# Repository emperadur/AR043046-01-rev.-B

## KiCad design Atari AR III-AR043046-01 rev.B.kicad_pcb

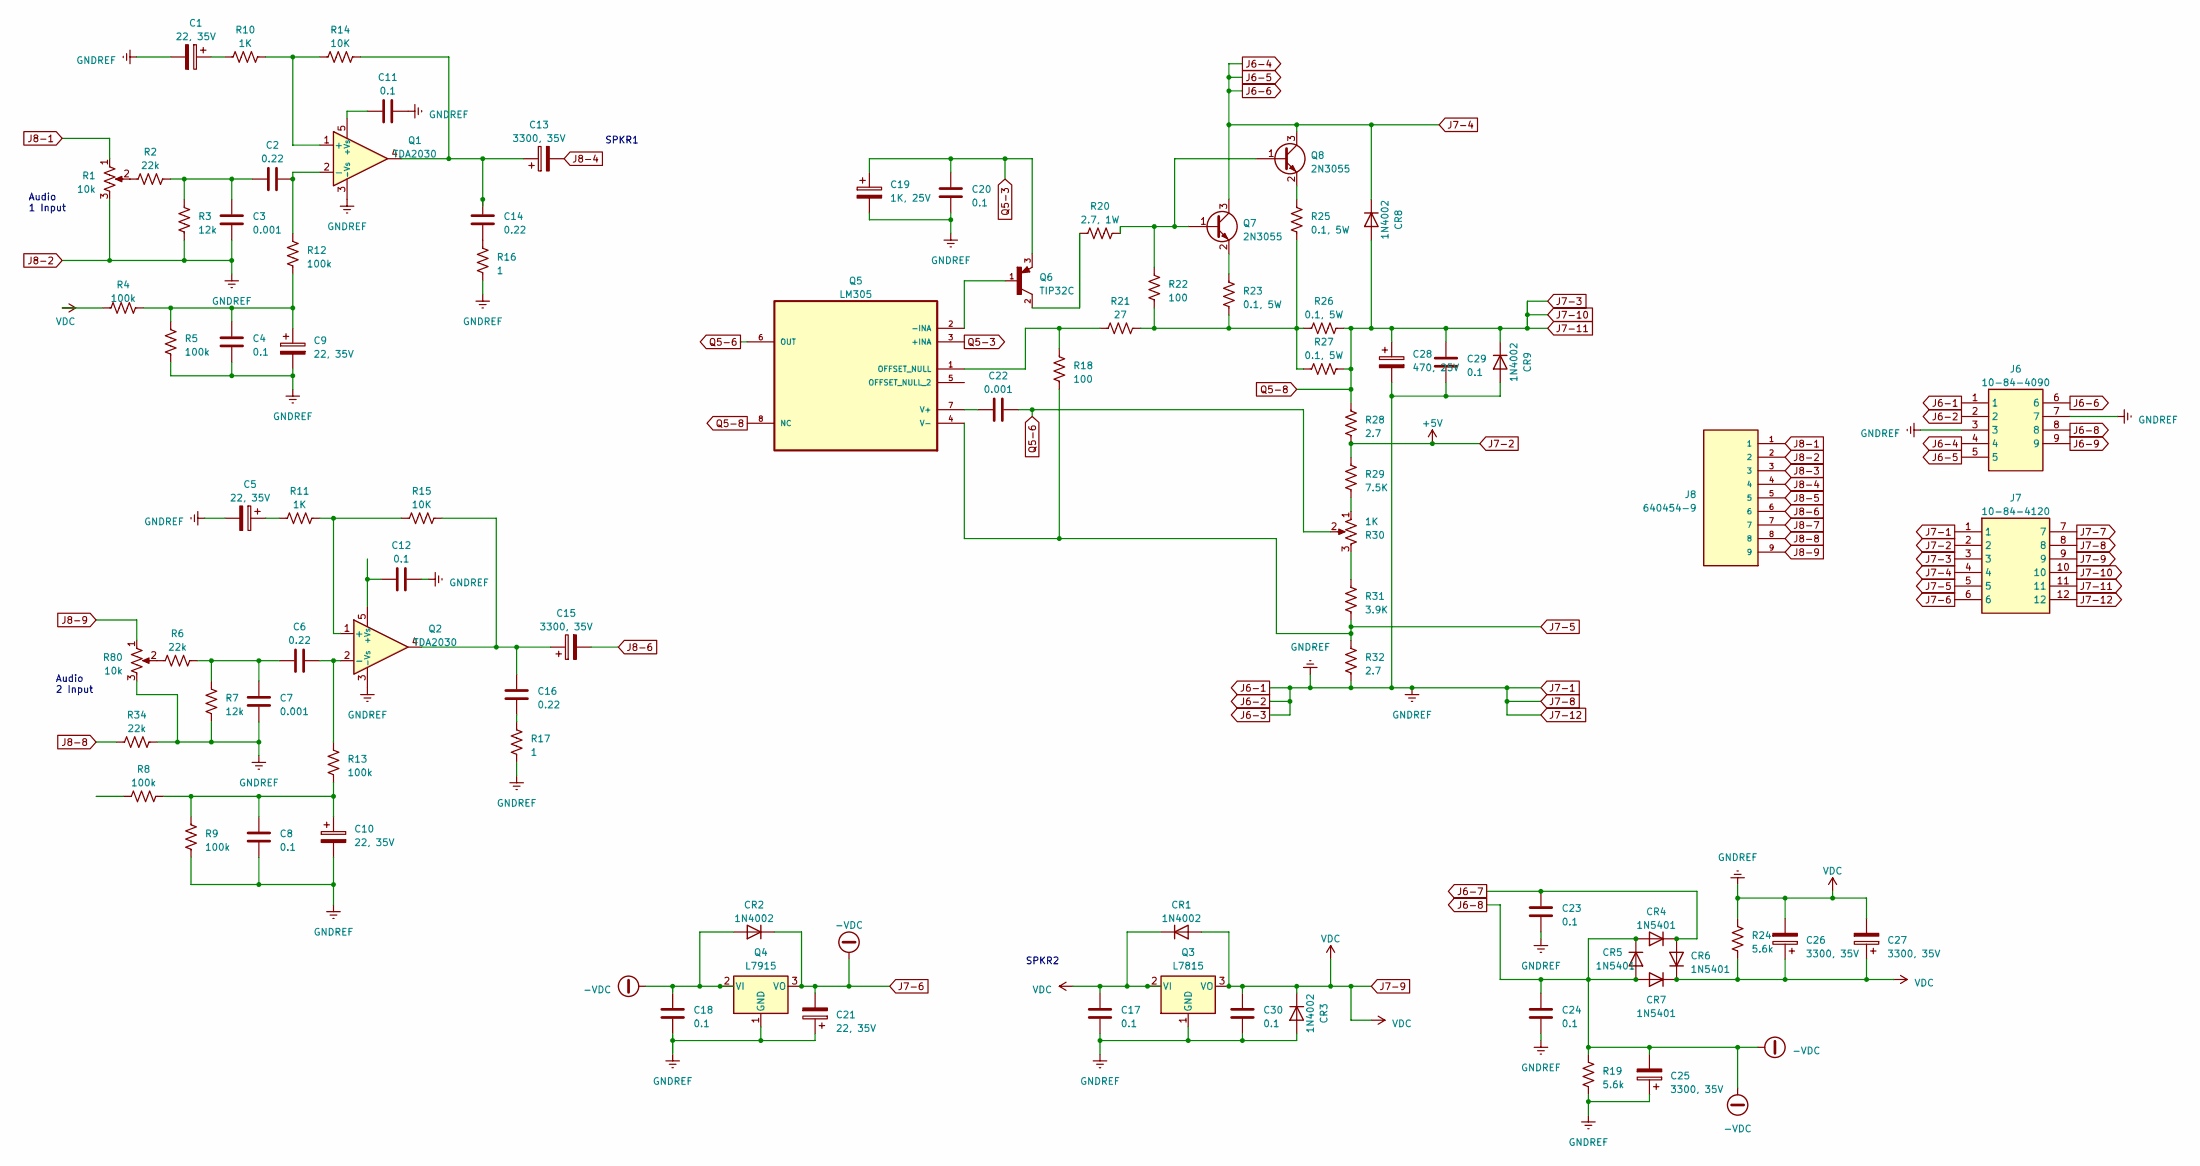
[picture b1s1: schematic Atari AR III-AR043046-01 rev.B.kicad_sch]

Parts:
C1, C5, C9, C10, C21: 22, 35V; C_Axial_L17.0mm_D6.5mm_P20.00mm_Horizontal
C2: 0.22; C_Axial_L5.1mm_D3.1mm_P15.00mm_Horizontal
C3, C7, C22: 0.001; C_Axial_L3.8mm_D2.6mm_P12.50mm_Horizontal
C4, C8, C11, C12, C17, C18, C20, C23, C24, C29, C30: 0.1; C_Axial_L3.8mm_D2.6mm_P12.50mm_Horizontal
C6, C14, C16: 0.22; C_Axial_L12.0mm_D6.5mm_P20.00mm_Horizontal
C13, C15, C25, C26, C27: 3300, 35V; CP_Axial_L55.0mm_D23.0mm_P60.00mm_Horizontal
C19: 1K, 25V; CP_Axial_L29.0mm_D10.0mm_P35.00mm_Horizontal
C28: 470, 25V; CP_Axial_L29.0mm_D10.0mm_P35.00mm_Horizontal
CR1, CR2, CR3, CR8, CR9: 1N4002; D_DO-41_SOD81_P10.16mm_Horizontal
CR4, CR5, CR6, CR7: 1N5401; D_DO-201AD_P15.24mm_Horizontal
J6: 10-84-4090; 10844090; Manufacturer_Part_Number 10-84-4090; Mouser Part Number 538-10-84-4090
J7: 10-84-4120; 10844120; Manufacturer_Part_Number 10-84-4120; Mouser Part Number 538-10-84-4120
J8: 640454-9; TE_640454-9
Q1, Q2: TDA2030; TO-220-5_P3.4x3.7mm_StaggerOdd_Lead3.8mm_Vertical
Q3: L7815; TO-220-3_Vertical
Q4: L7915; TO-220-3_Vertical
Q5: LM305; TO-99-8; MPN LM741CH/NOPB
Q6: TIP32C; TO-220-3_Vertical; PARTREV 2
Q7, Q8: 2N3055; TO-3
R1: 10k; Potentiometer_Bourns_3386P_Vertical
R2, R6, R34: 22k; R_Axial_DIN0309_L9.0mm_D3.2mm_P12.70mm_Horizontal
R3, R7: 12k; R_Axial_DIN0309_L9.0mm_D3.2mm_P12.70mm_Horizontal
R4, R5, R8, R9, R12, R13: 100k; R_Axial_DIN0309_L9.0mm_D3.2mm_P12.70mm_Horizontal
R10, R11: 1K; R_Axial_DIN0309_L9.0mm_D3.2mm_P12.70mm_Horizontal
R14, R15: 10K; R_Axial_DIN0309_L9.0mm_D3.2mm_P12.70mm_Horizontal
R16, R17: 1; R_Axial_DIN0309_L9.0mm_D3.2mm_P12.70mm_Horizontal
R18, R22: 100; R_Axial_DIN0309_L9.0mm_D3.2mm_P12.70mm_Horizontal
R19, R24: 5.6k; R_Axial_DIN0309_L9.0mm_D3.2mm_P12.70mm_Horizontal
R20: 2.7, 1W; R_Axial_DIN0411_L9.9mm_D3.6mm_P20.32mm_Horizontal
R21: 27; R_Axial_DIN0309_L9.0mm_D3.2mm_P12.70mm_Horizontal
R23, R25, R26, R27: 0.1, 5W; R_Axial_Power_L20.0mm_W6.4mm_P30.48mm
R28, R32: 2.7; R_Axial_DIN0309_L9.0mm_D3.2mm_P12.70mm_Horizontal
R29: 7.5K; R_Axial_DIN0309_L9.0mm_D3.2mm_P12.70mm_Horizontal
R30: 1K; Potentiometer_Bourns_3386P_Vertical
R31: 3.9K; R_Axial_DIN0309_L9.0mm_D3.2mm_P12.70mm_Horizontal
R80: 10k

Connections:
J6-1: C1.2, C3.2, C4.2, C5.2, C7.2, C8.2, C9.2, C10.2, C11.2, C12.2, C17.1, C17.2, C18.1, C19.2, C20.2, C21.1, C23.1, C24.1, C25.1, C26.1, C26.2, C27.1, C27.2, C28.2, C29.2, C30.1, C30.2, CR1.1 (K), CR1.2 (A), CR3.1 (K), CR3.2 (A), CR6.1 (K), CR7.1 (K), CR9.2 (A), J6.1, J6.2, J6.3, J6.7, J7.1, J7.8, J7.9, J7.12, J8.2, Q1.3 (-Vs), Q2.3 (-Vs), Q3.1 (GND), Q3.2 (VI), Q3.3 (VO), Q4.1 (GND), R1.3, R3.2, R4.1, R5.2, R7.2, R9.2, R16.2, R17.1, R19.1, R24.1, R24.2, R32.1, R34.2, R80.3
J6-4: CR8.1 (K), J6.4, J6.5, J6.6, J7.4, Q7.3 (C), Q8.3 (C)
J6-7: C23.2, CR4.1 (K), CR6.2 (A)
J6-8: C18.2, C21.2, C24.2, C25.2, CR2.1 (K), CR2.2 (A), CR4.2 (A), CR5.1 (K), CR5.2 (A), CR7.2 (A), J6.8, J7.6, Q4.2 (VI), Q4.3 (VO), R19.2
J6-9: J6.9
J7-2: J7.2, R28.1, R29.2
J7-5: J7.5, Q5.4 (V-), R18.2, R31.1, R32.2
J7-7: J7.7
J7-10: C28.1, C29.1, CR8.2 (A), CR9.1 (K), J7.3, J7.10, J7.11, Q5.8 (NC), R26.2, R27.2, R28.2
J8-1: J8.1, R1.1
J8-3: J8.3
J8-4: C13.2, J8.4
J8-5: J8.5
J8-6: C15.2, J8.6
J8-7: J8.7
J8-8: J8.8, R34.1
J8-9: J8.9, R80.1
unnamed: C1.1, R10.1
unnamed: C2.1, C3.1, R2.2, R3.1
unnamed: C4.1, C9.1, R4.2, R5.1, R12.2
unnamed: C5.1, R11.1
unnamed: C6.1, C7.1, R6.2, R7.1
unnamed: C8.1, C10.1, R8.2, R9.1, R13.2
unnamed: C13.1, C14.1, Q1.4, R14.2
unnamed: C14.2, R16.1
unnamed: C15.1, C16.2, Q2.4, R15.2
unnamed: C16.1, R17.2
unnamed: Q1.1 (+), R10.2, R14.1
unnamed: C11.1, Q1.5 (+Vs)
unnamed: C2.2, Q1.2 (-), R12.1
unnamed: Q2.1 (+), R11.2, R15.1
unnamed: C12.1, Q2.5 (+Vs)
unnamed: C6.2, Q2.2 (-), R13.1
unnamed: Q5.2 (-INA), Q6.1
unnamed: Q5.1 (OFFSET_NULL), R18.1, R21.1
unnamed: C22.2, Q5.7 (V+)
unnamed: Q6.2, R20.1
unnamed: Q7.1 (B), Q8.1 (B), R20.2, R22.1
unnamed: Q7.2 (E), R23.1
unnamed: Q8.2 (E), R25.1
unnamed: R1.2, R2.1
unnamed: R6.1, R80.2
unnamed: R21.2, R22.2, R23.2, R25.2, R26.1, R27.1
unnamed: R29.1, R30.1
unnamed: R30.3, R31.2
Q5-3: C19.1, C20.1, Q5.3 (+INA), Q6.3
Q5-6: C22.1, Q5.6 (OUT), R30.2

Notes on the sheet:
Audio 1 Input
SPKR2
Audio 2 Input
SPKR1

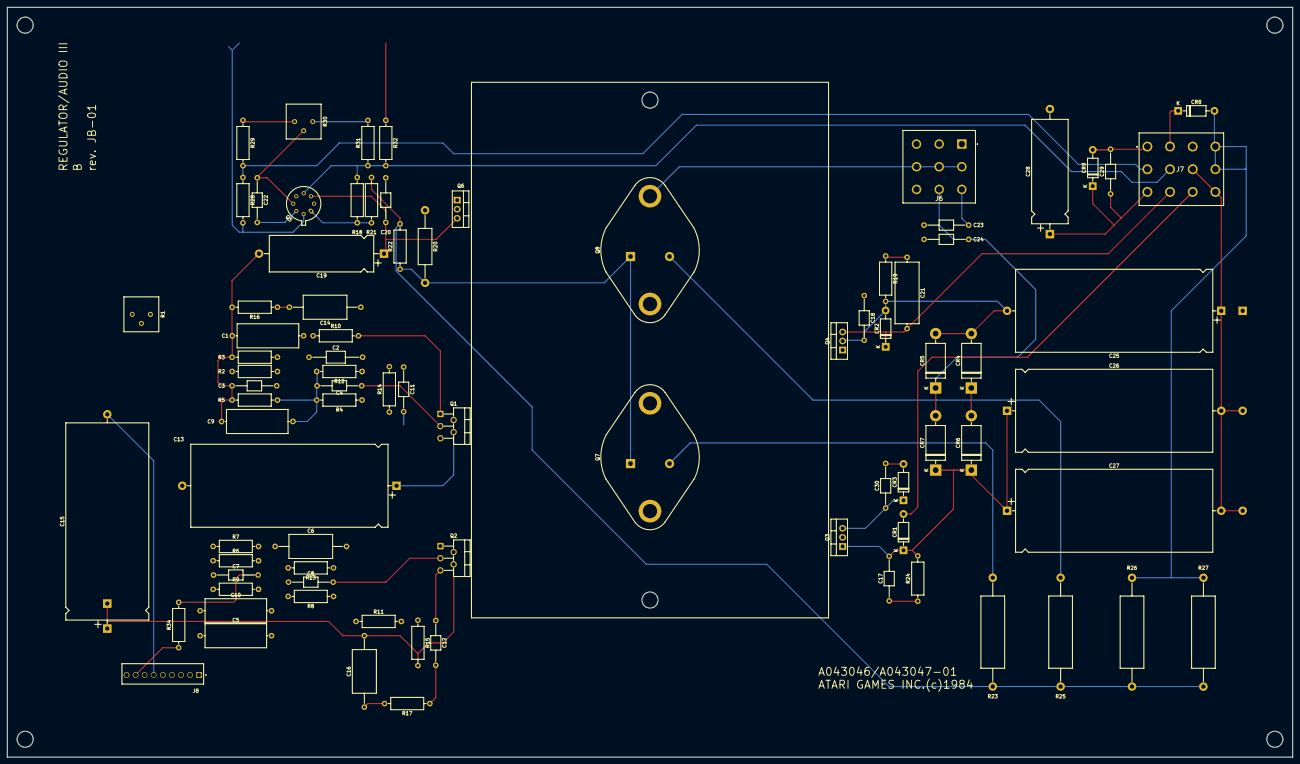
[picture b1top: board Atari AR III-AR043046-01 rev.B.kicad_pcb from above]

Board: 2 copper layers, 360.0 x 210.0 mm, 83 parts (0 on the bottom side), 40 nets.

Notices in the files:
Atari AR III-AR043046-01 rev.B.kicad_pcb:
ATARI GAMES INC.(c)1984
